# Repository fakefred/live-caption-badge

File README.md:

# Live Caption Badge

The Live Caption Badge is my team's capstone project for EECS 473, from
September to December 2024. It is a device that transmits and transcribes
speech in a noisy environment in real-time for the hard of hearing.

For technical details, please read [our report](report.pdf) (10.6 MiB).

## Technical Highlights

- ESP32 with ESP-IDF and ESP-ADF
- FreeRTOS
- Audio streaming over HTTP
- Peer discovery over BLE
- Real-time speech-to-text with Vosk
- E-Paper over SPI
- Audio over I2S

## Files

- `firmware` is the firmware our product actually ran on Design Expo.
- `audio`, `BLEnWifi`, `echo`, `epaper` contain the code we used to test
  various components.
- `pcb` is our PCB design. It is a 4-layer board.
- `transcribe` contains the code for the central server `server_esp.py`,
  which ran on a laptop on Design Expo. It is responsible for transcribing
  text and relaying audio. We also used `hack.py` to apply hotfixes to the
  badges.

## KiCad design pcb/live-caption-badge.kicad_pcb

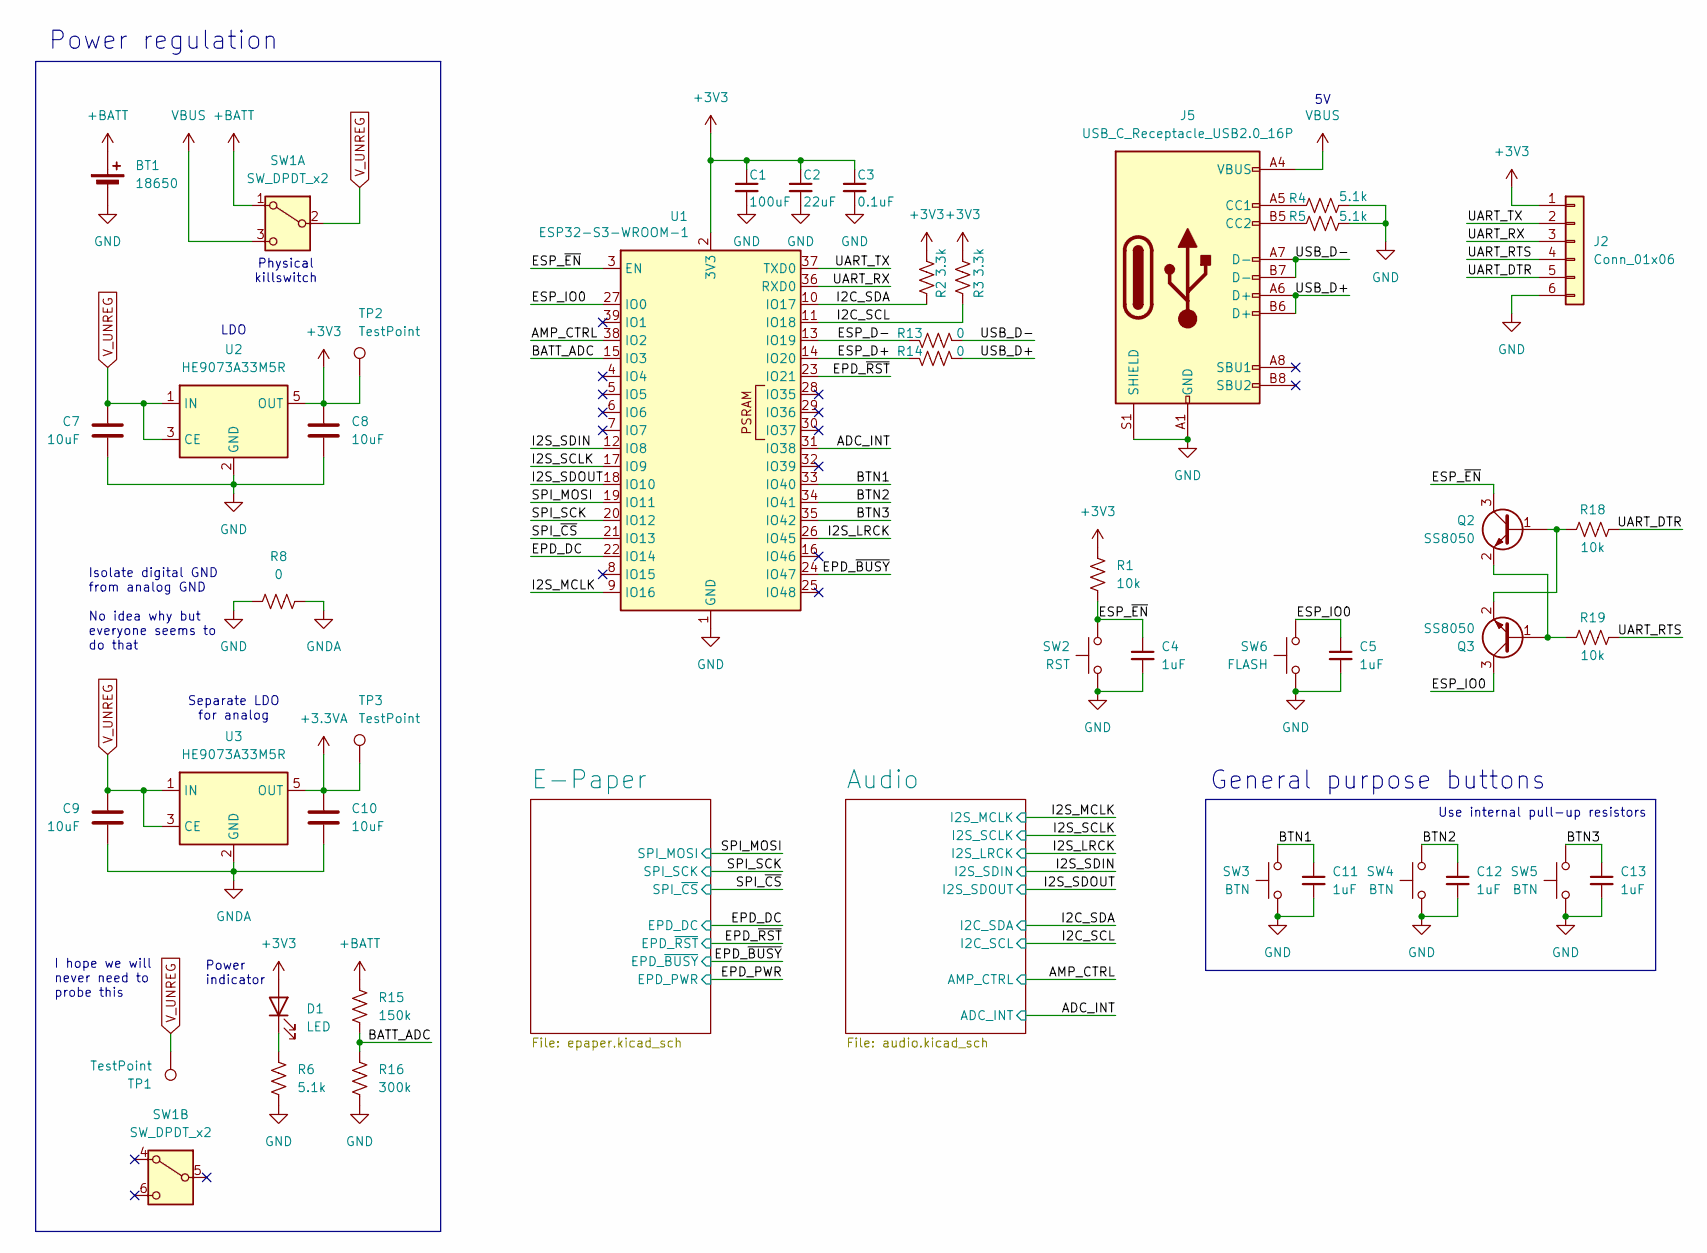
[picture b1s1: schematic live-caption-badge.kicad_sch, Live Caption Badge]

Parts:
BT1: 18650; BH-18650-B1BA002
C1: 100uF; CP_Radial_D8.0mm_P3.50mm
C2: 22uF; C_0603_1608Metric
C3: 0.1uF; C_0603_1608Metric
C4, C5, C11, C12, C13: 1uF; C_0603_1608Metric
C7, C8, C9, C10: 10uF; C_0603_1608Metric
D1: LED; LED_0603_1608Metric
J2: Conn_01x06; PinHeader_1x06_P2.54mm_Vertical
J5: USB_C_Receptacle_USB2.0_16P; USB_C_Receptacle_Molex_2169900002
Q2, Q3: SS8050; SOT-23
R1, R18, R19: 10k; R_0603_1608Metric
R2, R3: 3.3k; R_0603_1608Metric
R4, R5, R6: 5.1k; R_0603_1608Metric
R8, R13, R14: 0; R_0603_1608Metric
R15: 150k; R_0603_1608Metric
R16: 300k; R_0603_1608Metric
SW1: SW_DPDT_x2; SW_DPDT_SLW-867569-4A-N-D
SW2: RST; SW_Push_6x3mm
SW3, SW4, SW5: BTN; SW_Push_TL1100CF160Q
SW6: FLASH; SW_Push_6x3mm
TP1, TP2, TP3: TestPoint; PinHeader_1x01_P2.54mm_Vertical
U1: ESP32-S3-WROOM-1; ESP32-S3-WROOM-1-LargerVias
U2, U3: HE9073A33M5R; SOT-23-5

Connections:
+3.3VA: C10.1, TP3.1, U3.5 (OUT); also elsewhere on the board
+3V3: C1.1, C2.1, C3.1, C8.1, D1.2 (A), J2.1, R1.1, R2.1, R3.1, TP2.1, U1.2 (3V3), U2.5 (OUT); also elsewhere on the board
+BATT: BT1.1 (+), R15.2, SW1.1 (A)
/ADC_INT: U1.31 (IO38); also elsewhere on the board
/AMP_CTRL: U1.38 (IO2); also elsewhere on the board
/BATT_ADC: R15.1, R16.2, U1.15 (IO3)
/BTN1: C11.1, SW3.2, U1.33 (IO40)
/BTN2: C12.1, SW4.2, U1.34 (IO41)
/BTN3: C13.1, SW5.2, U1.35 (IO42)
/EPD_DC: U1.22 (IO14); also elsewhere on the board
/EPD_~BUSY: U1.24 (IO47); also elsewhere on the board
/EPD_~RST: U1.23 (IO21); also elsewhere on the board
/ESP_D+: R14.2, U1.14 (IO20)
/ESP_D-: R13.2, U1.13 (IO19)
/ESP_IO0: C5.1, Q3.3 (C), SW6.2, U1.27 (IO0)
/ESP_~EN: C4.1, Q2.3 (C), R1.2, SW2.2, U1.3 (EN)
/I2C_SCL: R3.2, U1.11 (IO18); also elsewhere on the board
/I2C_SDA: R2.2, U1.10 (IO17); also elsewhere on the board
/I2S_LRCK: U1.26 (IO45); also elsewhere on the board
/I2S_MCLK: U1.9 (IO16); also elsewhere on the board
/I2S_SCLK: U1.17 (IO9); also elsewhere on the board
/I2S_SDIN: U1.12 (IO8); also elsewhere on the board
/I2S_SDOUT: U1.18 (IO10); also elsewhere on the board
/SPI_MOSI: U1.19 (IO11); also elsewhere on the board
/SPI_SCK: U1.20 (IO12); also elsewhere on the board
/SPI_~CS: U1.21 (IO13); also elsewhere on the board
/UART_DTR: J2.5, R18.2
/UART_RTS: J2.4, R19.2
/UART_RX: J2.3, U1.36 (RXD0)
/UART_TX: J2.2, U1.37 (TXD0)
/USB_D+: J5.A6 (D+), J5.B6 (D+), R14.1
/USB_D-: J5.A7 (D-), J5.B7 (D-), R13.1
GND: BT1.2 (-), C1.2, C2.2, C3.2, C4.2, C5.2, C7.2, C8.2, C11.2, C12.2, C13.2, J2.6, J5.A1 (GND), J5.A12 (GND), J5.B1 (GND), J5.B12 (GND), J5.S1 (SHIELD), R4.2, R5.2, R6.1, R8.1, R16.1, SW2.1, SW3.1, SW4.1, SW5.1, SW6.1, U1.1 (GND), U1.40 (GND), U1.41 (GND), U2.2 (GND); also elsewhere on the board
GNDA: C9.2, C10.2, R8.2, U3.2 (GND); also elsewhere on the board
unnamed: D1.1 (K), R6.2
unnamed: J5.A5 (CC1), R4.1
unnamed: J5.B5 (CC2), R5.1
unnamed: Q2.1 (B), Q3.2 (E), R18.1
unnamed: Q2.2 (E), Q3.1 (B), R19.1
VBUS: J5.A4 (VBUS), J5.A9 (VBUS), J5.B4 (VBUS), J5.B9 (VBUS), SW1.3 (C)
V_UNREG: C7.1, C9.1, SW1.2 (B), TP1.1, U2.1 (IN), U2.3 (CE), U3.1 (IN), U3.3 (CE)

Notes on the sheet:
Power regulation
Physical killswitch
LDO
I hope we will never need to probe this
Power indicator
Use internal pull-up resistors
General purpose buttons
Isolate digital GND from analog GND No idea why but everyone seems to do that
Separate LDO for analog

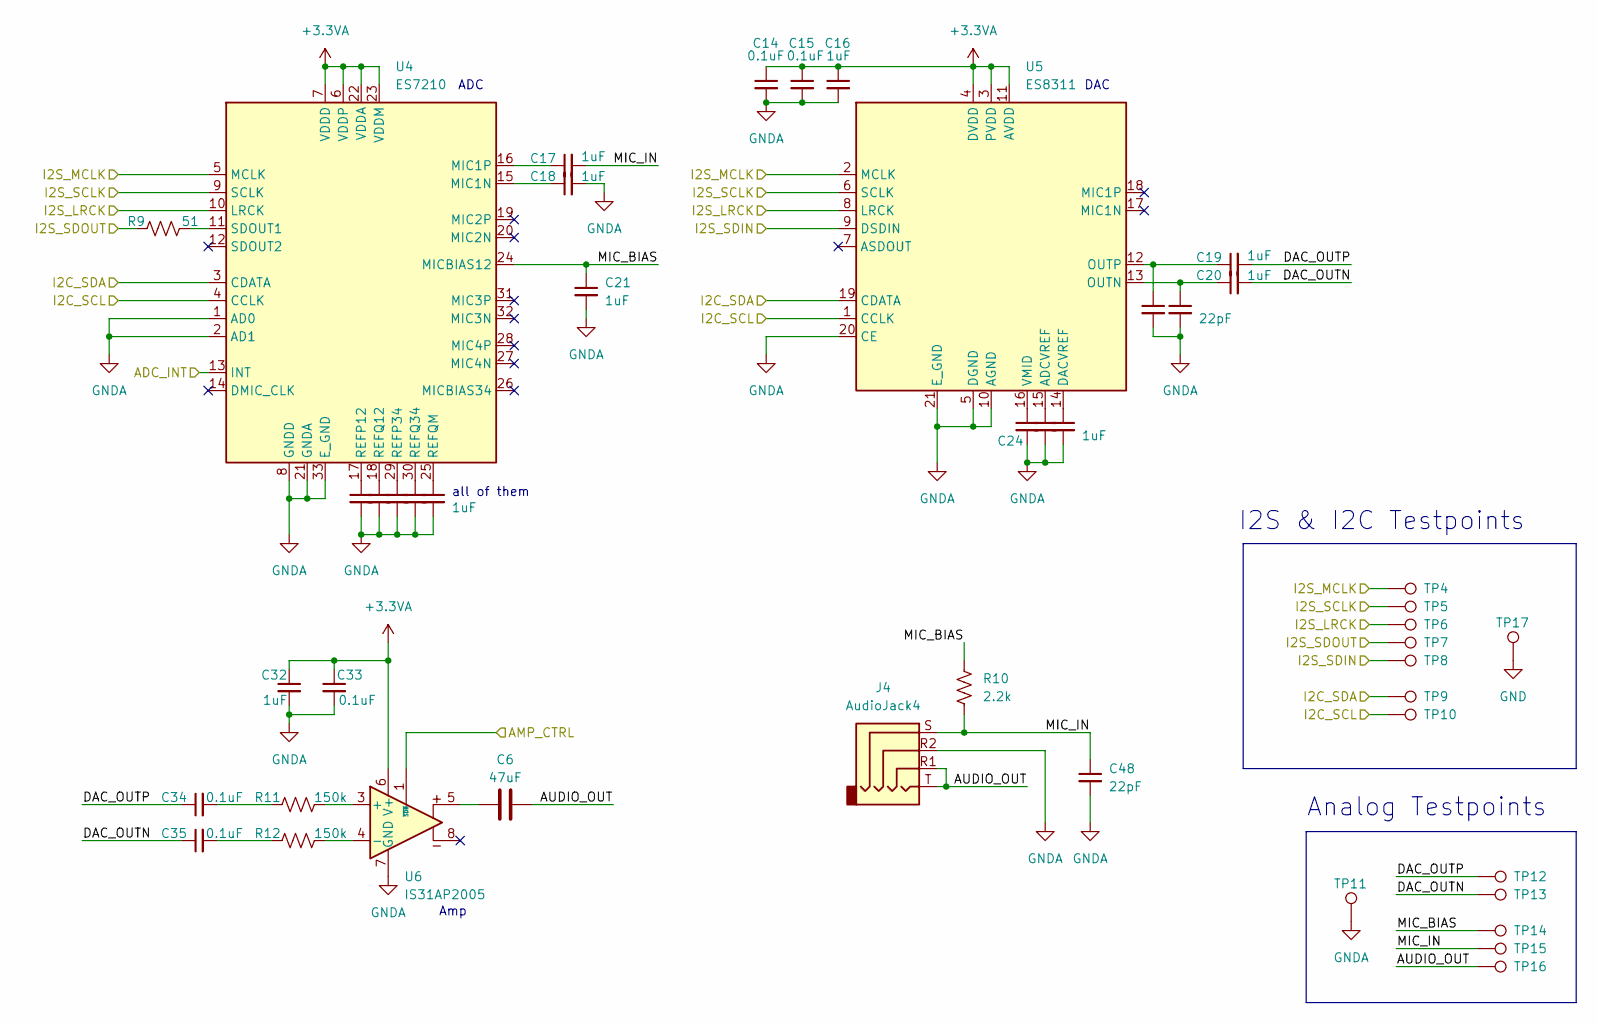
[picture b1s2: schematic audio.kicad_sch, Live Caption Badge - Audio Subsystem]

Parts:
C6: 47uF; C_0603_1608Metric
C14, C15, C33, C34, C35: 0.1uF; C_0603_1608Metric
C16, C17, C18, C19, C20, C21, C24, C25, C26, C27, C28, C29, C30, C31, C32: 1uF; C_0603_1608Metric
C22, C23, C48: 22pF; C_0603_1608Metric
J4: AudioJack4; Jack_3.5mm_PJ320D_Horizontal
R9: 51; R_0603_1608Metric
R10: 2.2k; R_0603_1608Metric
R11, R12: 150k; R_0603_1608Metric
TP4, TP5, TP6, TP7, TP8, TP9, TP10, TP11, TP12, TP13, TP14, TP15, TP16, TP17: TestPoint; PinHeader_1x01_P2.54mm_Vertical
U4: ES7210; QFN-32-1EP_4x4mm_P0.4mm_EP2.9x2.9mm
U5: ES8311; QFN-20-1EP_3x3mm_P0.4mm_EP1.65x1.65mm
U6: IS31AP2005; MSOP-8_3x3mm_P0.65mm

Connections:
+3.3VA: C14.1, C15.1, C16.1, C32.1, C33.1, U4.6 (VDDP), U4.7 (VDDD), U4.22 (VDDA), U4.23 (VDDM), U5.3 (PVDD), U5.4 (DVDD), U5.11 (AVDD), U6.6 (V+); also elsewhere on the board
/ADC_INT: U4.13 (INT); also elsewhere on the board
/AMP_CTRL: U6.1 (~SDB); also elsewhere on the board
/Audio/AUDIO_OUT: C6.2, J4.R1, J4.T, TP16.1
/Audio/DAC_OUTN: C20.2, C35.1, TP13.1
/Audio/DAC_OUTP: C19.2, C34.1, TP12.1
/Audio/MIC_BIAS: C21.1, R10.1, TP14.1, U4.24 (MICBIAS12)
/Audio/MIC_IN: C17.2, C48.1, J4.S, R10.2, TP15.1
/I2C_SCL: TP10.1, U4.4 (CCLK), U5.1 (CCLK); also elsewhere on the board
/I2C_SDA: TP9.1, U4.3 (CDATA), U5.19 (CDATA); also elsewhere on the board
/I2S_LRCK: TP6.1, U4.10 (LRCK), U5.8 (LRCK); also elsewhere on the board
/I2S_MCLK: TP4.1, U4.5 (MCLK), U5.2 (MCLK); also elsewhere on the board
/I2S_SCLK: TP5.1, U4.9 (SCLK), U5.6 (SCLK); also elsewhere on the board
/I2S_SDIN: TP8.1, U5.9 (DSDIN); also elsewhere on the board
/I2S_SDOUT: R9.1, TP7.1; also elsewhere on the board
GND: TP17.1; also elsewhere on the board
GNDA: C14.2, C15.2, C16.2, C18.2, C21.2, C22.2, C23.2, C24.2, C25.2, C26.2, C27.2, C28.2, C29.2, C30.2, C31.2, C32.2, C33.2, C48.2, J4.R2, TP11.1, U4.1 (AD0), U4.2 (AD1), U4.8 (GNDD), U4.21 (GNDA), U4.33 (E_GND), U5.5 (DGND), U5.10 (AGND), U5.20 (CE), U5.21 (E_GND), U6.7 (GND); also elsewhere on the board
unnamed: C6.1, U6.5
unnamed: C34.2, R11.1
unnamed: C35.2, R12.1
unnamed: C18.1, U4.15 (MIC1N)
unnamed: C17.1, U4.16 (MIC1P)
unnamed: C27.1, U4.17 (REFP12)
unnamed: C29.1, U4.29 (REFP34)
unnamed: C28.1, U4.18 (REFQ12)
unnamed: C30.1, U4.30 (REFQ34)
unnamed: C31.1, U4.25 (REFQM)
unnamed: R9.2, U4.11 (SDOUT1)
unnamed: C25.1, U5.15 (ADCVREF)
unnamed: C26.1, U5.14 (DACVREF)
unnamed: C20.1, C23.1, U5.13 (OUTN)
unnamed: C19.1, C22.1, U5.12 (OUTP)
unnamed: C24.1, U5.16 (VMID)
unnamed: R11.2, U6.3 (+)
unnamed: R12.2, U6.4 (-)

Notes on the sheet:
DAC
all of them
Amp
Analog Testpoints
I2S & I2C Testpoints
ADC

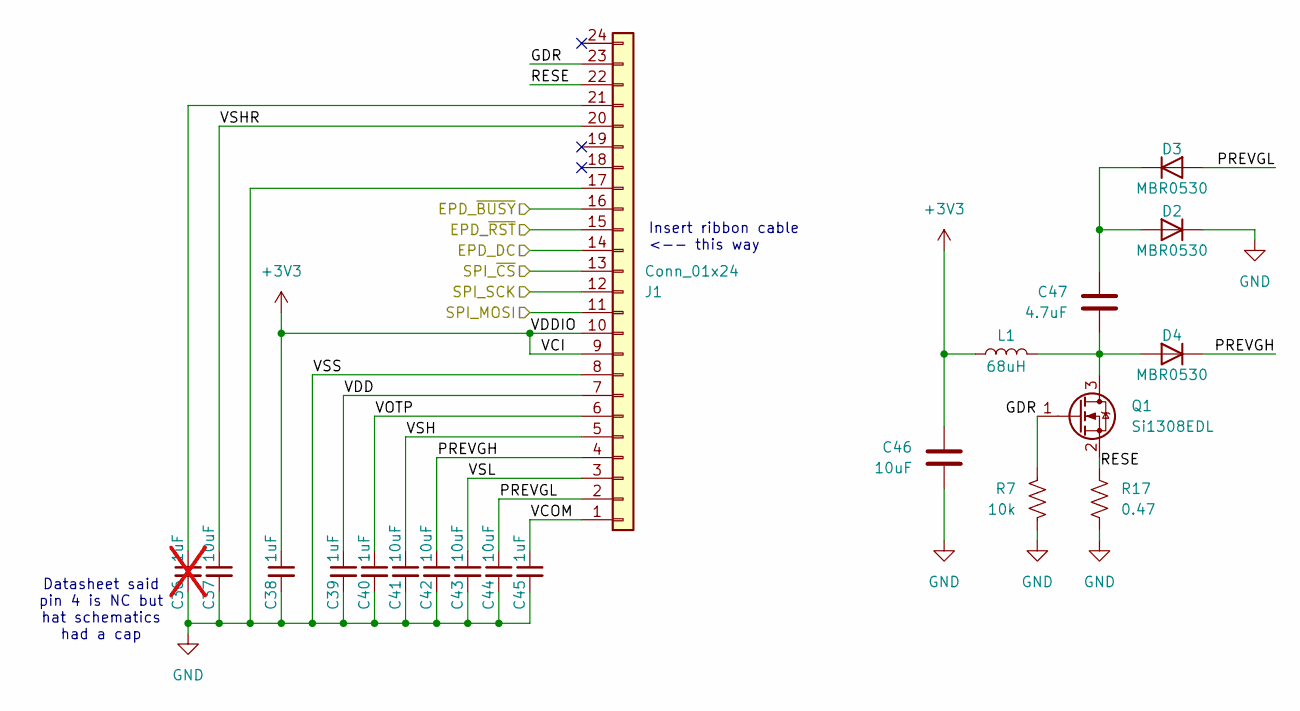
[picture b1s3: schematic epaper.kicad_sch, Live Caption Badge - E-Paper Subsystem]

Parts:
C36: 1uF; C_0603_1608Metric; not fitted
C37, C41, C42, C43, C44, C46: 10uF; C_0603_1608Metric
C38, C39, C40, C45: 1uF; C_0603_1608Metric
C47: 4.7uF; C_0603_1608Metric
D2, D3, D4: MBR0530; D_SOD-123
J1: Conn_01x24; FPC05024-13200_1x24-1MP_P0.50_Horizontal
L1: 68uH; L_Bourns-SDEE0406A
Q1: Si1308EDL; SOT-323_SC-70
R7: 10k; R_0603_1608Metric
R17: 0.47; R_0603_1608Metric

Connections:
+3V3: C38.1, C46.1, J1.9, J1.10, L1.1; also elsewhere on the board
/E-Paper/GDR: J1.23, Q1.1 (G), R7.1
/E-Paper/PREVGH: C42.1, D4.1 (K), J1.4
/E-Paper/PREVGL: C44.1, D3.2 (A), J1.2
/E-Paper/RESE: J1.22, Q1.2 (S), R17.1
/E-Paper/VCOM: C45.1, J1.1
/E-Paper/VDD: C39.1, J1.7
/E-Paper/VOTP: C40.1, J1.6
/E-Paper/VSH: C41.1, J1.5
/E-Paper/VSHR: C37.1, J1.20
/E-Paper/VSL: C43.1, J1.3
/EPD_DC: J1.14; also elsewhere on the board
/EPD_~BUSY: J1.16; also elsewhere on the board
/EPD_~RST: J1.15; also elsewhere on the board
/SPI_MOSI: J1.11; also elsewhere on the board
/SPI_SCK: J1.12; also elsewhere on the board
/SPI_~CS: J1.13; also elsewhere on the board
GND: C36.2, C37.2, C38.2, C39.2, C40.2, C41.2, C42.2, C43.2, C44.2, C45.2, C46.2, D2.1 (K), J1.8, J1.17, R7.2, R17.2; also elsewhere on the board
unnamed: C47.1, D2.2 (A), D3.1 (K)
unnamed: C47.2, D4.2 (A), L1.2, Q1.3 (D)
unnamed: C36.1, J1.21

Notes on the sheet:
Datasheet said pin 4 is NC but hat schematics had a cap
Insert ribbon cable <-- this way

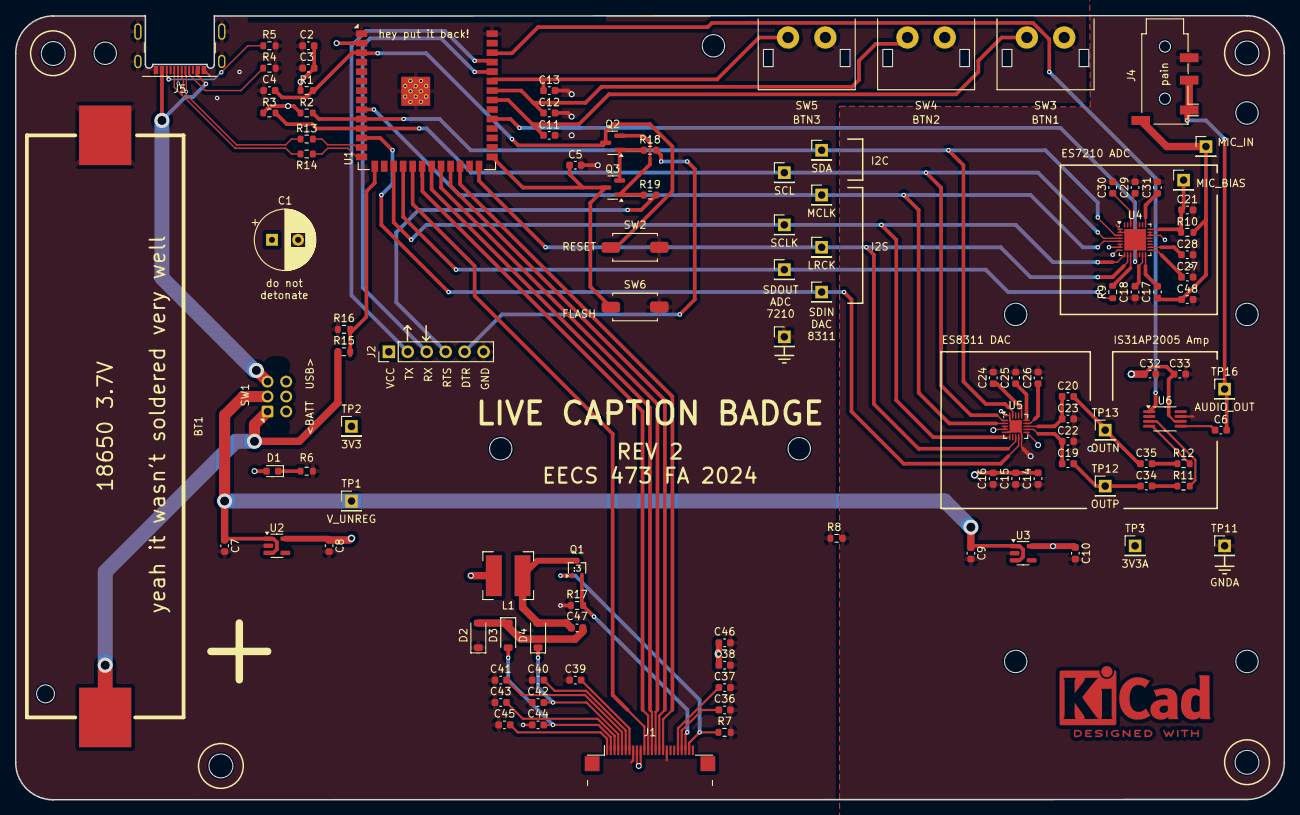
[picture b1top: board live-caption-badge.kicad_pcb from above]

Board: 4 copper layers, 170.0 x 105.1 mm, 109 parts (0 on the bottom side), 77 nets.

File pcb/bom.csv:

Reference,Value,Qty
BT1,,1
C1,100uF,1
C2,22uF,1
"C3,C14,C15,C33,C34,C35",0.1uF,6
"C4,C5,C11-C13,C16-C21,C24-C32,C38-C40,C45",1uF,24
C6,47uF,1
"C7-C10,C37,C41-C44,C46",10uF,10
"C22,C23,C48",22pF,3
C36,NC,1
C47,4.7uF,1
D1,LED,1
"D2,D3,D4",MBR0530,3
J1,FPC24,1
J2,Conn_01x06,1
J4,AudioJack4,1
J5,USB_C_Receptacle_USB2.0_16P,1
L1,68uH,1
Q1,Si1308EDL,1
"Q2,Q3",SS8050,2
"R1,R7,R18,R19",10k,4
"R2,R3",3.3k,2
"R4,R5,R6",5.1k,3
"R8,R13,R14",0,3
R9,51,1
R10,2.2k,1
"R11,R12,R15",150k,3
R16,300k,1
R17,0.47,1
SW1,SW_DPDT_x2,1
SW2,RST,1
"SW3,SW4,SW5",BTN,3
SW6,FLASH,1
TP1-TP17,TestPoint,17
U1,ESP32-S3-WROOM-1,1
"U2,U3",HE9073A33M5R,2
U4,ES7210,1
U5,ES8311,1
U6,IS31AP2005,1

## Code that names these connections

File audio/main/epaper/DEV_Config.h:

/*****************************************************************************
* | File      	:   DEV_Config.h
* | Author      :   Waveshare team
* | Function    :   Hardware underlying interface
* | Info        :
*----------------
* |	This version:   V1.0
* | Date        :   2020-02-19
* | Info        :
#
# Permission is hereby granted, free of charge, to any person obtaining a copy
# of this software and associated documnetation files (the "Software"), to deal
# in the Software without restriction, including without limitation the rights
# to use, copy, modify, merge, publish, distribute, sublicense, and/or sell
# copies of the Software, and to permit persons to  whom the Software is
# furished to do so, subject to the following conditions:
#
# The above copyright notice and this permission notice shall be included in
# all copies or substantial portions of the Software.
#
# THE SOFTWARE IS PROVIDED "AS IS", WITHOUT WARRANTY OF ANY KIND, EXPRESS OR
# IMPLIED, INCLUDING BUT NOT LIMITED TO THE WARRANTIES OF MERCHANTABILITY,
# FITNESS OR A PARTICULAR PURPOSE AND NONINFRINGEMENT. IN NO EVENT SHALL THE
# AUTHORS OR COPYRIGHT HOLDERS BE LIABLE FOR ANY CLAIM, DAMAGES OR OTHER
# LIABILITY WHETHER IN AN ACTION OF CONTRACT, TORT OR OTHERWISE, ARISING FROM,
# OUT OF OR IN CONNECTION WITH THE SOFTWARE OR THE USE OR OTHER DEALINGS IN
# THE SOFTWARE.
#
******************************************************************************/
#ifndef _DEV_CONFIG_H_
#define _DEV_CONFIG_H_

#include "driver/gpio.h"
#include "freertos/FreeRTOS.h"
#include "SPI.h"
#include <stdint.h>
#include <stdio.h>

/**
 * data
 **/
#define UBYTE uint8_t
#define UWORD uint16_t
#define UDOUBLE uint32_t

/**
 * GPIO config
 **/
#define EPD_SCK_PIN GPIO_NUM_12
#define EPD_MOSI_PIN GPIO_NUM_11
#define EPD_MISO_PIN GPIO_NUM_48 // unused
#define EPD_CS_PIN GPIO_NUM_13
#define EPD_RST_PIN GPIO_NUM_21
#define EPD_DC_PIN GPIO_NUM_14
#define EPD_BUSY_PIN GPIO_NUM_47
#define EPD_PWR_PIN GPIO_NUM_7

#define GPIO_PIN_SET 1
#define GPIO_PIN_RESET 0

#define HIGH 1
#define LOW 0

/**
 * GPIO read and write
 **/
#define DEV_Digital_Write(_pin, _value) gpio_set_level(_pin, _value)
#define DEV_Digital_Read(_pin) gpio_get_level(_pin)

/**
 * delay x ms
 **/
#define DEV_Delay_ms(__xms) vTaskDelay(pdMS_TO_TICKS(__xms))

/*------------------------------------------------------------------------------------------------------*/
UBYTE DEV_Module_Init(void);
void  GPIO_Mode(UWORD GPIO_Pin, UWORD Mode);
void  DEV_SPI_WriteByte(UBYTE data);
UBYTE DEV_SPI_ReadByte();
void  DEV_SPI_Write_nByte(UBYTE *pData, UDOUBLE len);

#endif

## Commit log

2024-10-23 pcb: Add ES7210
2024-10-23 pcb: moved things around
2024-10-23 epaper driver schematic
2024-10-23 epaper driver
2024-10-23 pcb: Add ES8311
2024-10-23 clean files
2024-10-26 pcb: Audio subschematic seems done
2024-10-26 caps
2024-10-27 pcb: Schematics seem complete
2024-10-27 pcb: Renumber parts
2024-10-27 pcb: Assigned footprints (the more trivial ones)
2024-10-28 pcb: Begin layout
2024-10-28 pcb: More layout, design 18650 battery holder footprint
2024-10-29 pcb: I'm working in Spain but the S is silent
2024-10-30 pcb: 473 cannot defeat me in any way that matters
2024-10-30 pcb: pretty much done
2024-10-30 pcb: Fix misc footprints, add silkprint
2024-10-30 pcb: Checkpoint before incorporating Mark and James' suggestions
2024-10-30 pcb: Convert to 4-layer board
2024-10-31 [transcribe] upload python server and client.
2024-10-31 pcb: it may or may not work
2024-10-31 pcb: Yippee
2024-10-31 pcb: Slap a KiCad logo on it
2024-10-31 pcb: Rev 1 Gerbers
2024-10-31 new server
2024-10-31 pcb: Edit a couple R/C values, generate BOM
2024-11-04 server for transcribing wav file, pending experiment.
2024-11-05 modify reading frame part to handle the data, should work and pending sending suitable response.
2024-11-05 finished returning response with transcribed text on local file test, pending experiment on server. See test_simple.py for the main structure of dealing with a wav file input.
2024-11-06 server done with responding transcribed text.
2024-11-06 upload C code for recording and sending request.
2024-11-06 epaper: Port Arduino driver to esp-idf
2024-11-11 epaper: GPIO config
2024-11-13 epaper: Bee movie
2024-11-13 GET confirmed correct, still need to test robustness on POST and GET.
2024-11-13 Add a task to periodically send GET request to retreive transcribed result, and another task to print the current content of the buffer.
2024-11-13 epaper: font size 48
2024-11-13 SPI Driver + Interrupts
2024-11-13 epaper: README
2024-11-13 epaper: Reformat GUI_Paint.c
2024-11-13 epaper: Add logging points
2024-11-13 epaper: Remove commented out bit-banging code
2024-11-13 epaper: Use ESP_LOGE for error messages in GUI_Paint.c
2024-11-13 epaper: Remove redundant code
2024-11-13 epaper: Remove giant demo bitmap
2024-11-13 epaper: Reformat SPI.{c,h}
2024-11-14 epaper: Unify pin assignments in DEV_Config.h and SPI.h
2024-11-14 epaper: EPD_7IN5_V2_Display_Part now reads from full-screen framebuffer
2024-11-14 epaper: Implement caption abstraction with message buffer
2024-11-14 epaper: Refresh entire caption area every time
2024-11-14 epaper: Refresh smallest bounding box of all updated pixels in caption area
2024-11-14 epaper: Allow printing caption anywhere on screen
2024-11-14 epaper: Dynamic clear
2024-11-15 epaper: fix off by one
2024-11-20 epaper: Port to PCB
2024-11-20 epaper: PCB pin assignments
2024-11-20 playback: Import esp-adf example code play_mp3_control_example
2024-11-21 playback: why won't it work
2024-11-21 playback: lower volume
2024-11-21 playback: play wav
2024-11-21 recording: Enable ADC
2024-11-21 echo: whatever this is
2024-11-22 recording: fuck this im out
2024-11-22 pcb: Rev 2 schematic
2024-11-23 pcb: rev 2?
2024-11-23 recording: This version runs on the Korvo
2024-11-24 pcb: Flip FPC, 170x105mm
2024-11-24 pcb: move stuff
2024-11-25 esp-idf code to connect to wifi -> identify IPv4 address and advertise the address using GATT server.
2024-11-25 pcb: rev 2 ready?
2024-11-25 pcb: Rev 2 gerbers
2024-11-26 audio: play_mp3_control_example
2024-11-26 audio: echo example
2024-11-26 audio: echo example is now working
2024-11-26 audio_playback: Fixups
2024-11-26 audio: Rename audio_playback to audio
2024-11-26 meta: Update .gitignore
2024-11-26 audio: More cleanup
2024-11-26 audio: Attempt to do two-way HTTP
2024-11-26 epaper: Separate caption code into caption.c
2024-11-26 epaper: Move stuff around
2024-11-27 update server for threading, upload Blue & WiFi C file for code refactoring.
2024-11-27 enable two pipelines to send HTTP stream to multiple destinations.
2024-11-27 added IP address advertising(GATT Server) and GATT Client, pending testing on GATT Client.
2024-11-27 upload config file to build the project code, please use idf.py menuconfig, there is a load option in it.
2024-11-27 recovered commented periodically task.
2024-11-27 epaper: Allow toggling between badge mode and caption mode
2024-11-27 epaper: Rename bitmap.py -> font.py
2024-11-27 epaper: Rename bitmap.c.jinja -> font.c.jinja
2024-11-27 epaper: We can now toggle between badge and caption layouts
2024-11-28 epaper: Reorganize headers and write comments
2024-11-29 epaper: Manage refreshes with queue
2024-11-29 Display transcription on epaper
2024-11-29 transcription: Now the ESP is a server too
2024-11-29 echo: Make it separate for ease of testing
2024-11-30 audio: Clean out some garbage files
2024-11-30 audio: Rename http.{c,h} -> http_client.{c,h}
2024-11-30 epaper: Slow refresh when going back to badge mode
2024-11-30 Rudimentary pair layout
2024-12-01 audio: httpd_req_recv, weirdly, is not receiving
2024-12-01 audio: Peer TX via TCP
2024-12-02 Revert "audio: Peer TX via TCP"
    This reverts commit 603a1287deea83b019bbc07abee6595c515d0fba.
2024-12-02 audio: TO HELL WITH TCP AND ESP CHUNKED SERVER READS
2024-12-02 audio: Laptop sends chunked audio to ESP
2024-12-02 audio: Transmit audio from one ESP via laptop to another ESP
2024-12-02 the server now transmitts the transcribed partial results to the board.
2024-12-02 the server now transmitts partial results by sentences.
2024-12-02 audio: Auto start/stop RX with /poke endpoint and rx_http event handler
2024-12-02 audio: Redo server audio queue
2024-12-02 audio: FUCK IT WE BALL:wq
2024-12-03 epaper: Change pinout for rev 2
2024-12-03 transcribe: only POST when buffer is not empty
2024-12-03 audio: fix pinout
2024-12-03 transcribe: hardcode IPs
2024-12-03 pcb: Change paper size to US Letter
2024-12-03 files for BLE connection and Wifi connection.
2024-12-03 firmware: Unify everything we have
2024-12-03 firmware: Bunch of bitmaps
2024-12-03 epaper: Update bitmap.c.jinja
2024-12-03 epaper: Remove logo.c
2024-12-03 firmware: More layouts
2024-12-03 firmware: clang-format everything
2024-12-04 firmware: New buttons
2024-12-04 firmware: Reposition pairing icon
2024-12-04 used queue to store user data for app_main()
2024-12-04 firmware: Enable Amp only when RXing
2024-12-04 firmware: Merge Rain's queue-based GATT impl
2024-12-04 firmware: Pairing UI
2024-12-04 firmware: Thing (that I forgot)
2024-12-04 transcribe: Do not send POST /upload response
2024-12-04 firmware: transcription_post_handler dynamically allocates buffer; icons
2024-12-04 files for gatts, gattc, and wifi experiment.
2024-12-04 firmware: Even more pairing layouts
2024-12-04 firmware: RIP epaper_layout_t abstraction
2024-12-04 firmware: More pairing modes
2024-12-04 firmware: Merge Rain's gattc
2024-12-04 firmware: Fix misc text locations
2024-12-04 firmware: GATT shit
2024-12-04 create gatts_deinit() for restarting BLE functionality.
2024-12-04 firmware: Display peer name in badge layout
2024-12-04 firmware: Ready to merge Rain's new BLE
2024-12-04 transcribe: Check GET endpoints
2024-12-04 firmware: Merge Rain's GATT
2024-12-04 firmware: Minor text tweaks
2024-12-04 firmware: Unpoke
2024-12-05 updated the server to handle the pairing between the badges.
2024-12-05 transcribe: Do not write to WAV
2024-12-05 firmware: GET /reboot
2024-12-05 firmware: Whatever we have now
2024-12-05 transcribe: Remove bin
2024-12-05 hack.py
2024-12-09 firmware: /reboot and /user
2024-12-09 transcribe: hack
2024-12-09 meta: Credit images
2024-12-11 meta: Credit Krutarth Purohit for SPI.c
2025-02-26 Add report, update README before I forget
